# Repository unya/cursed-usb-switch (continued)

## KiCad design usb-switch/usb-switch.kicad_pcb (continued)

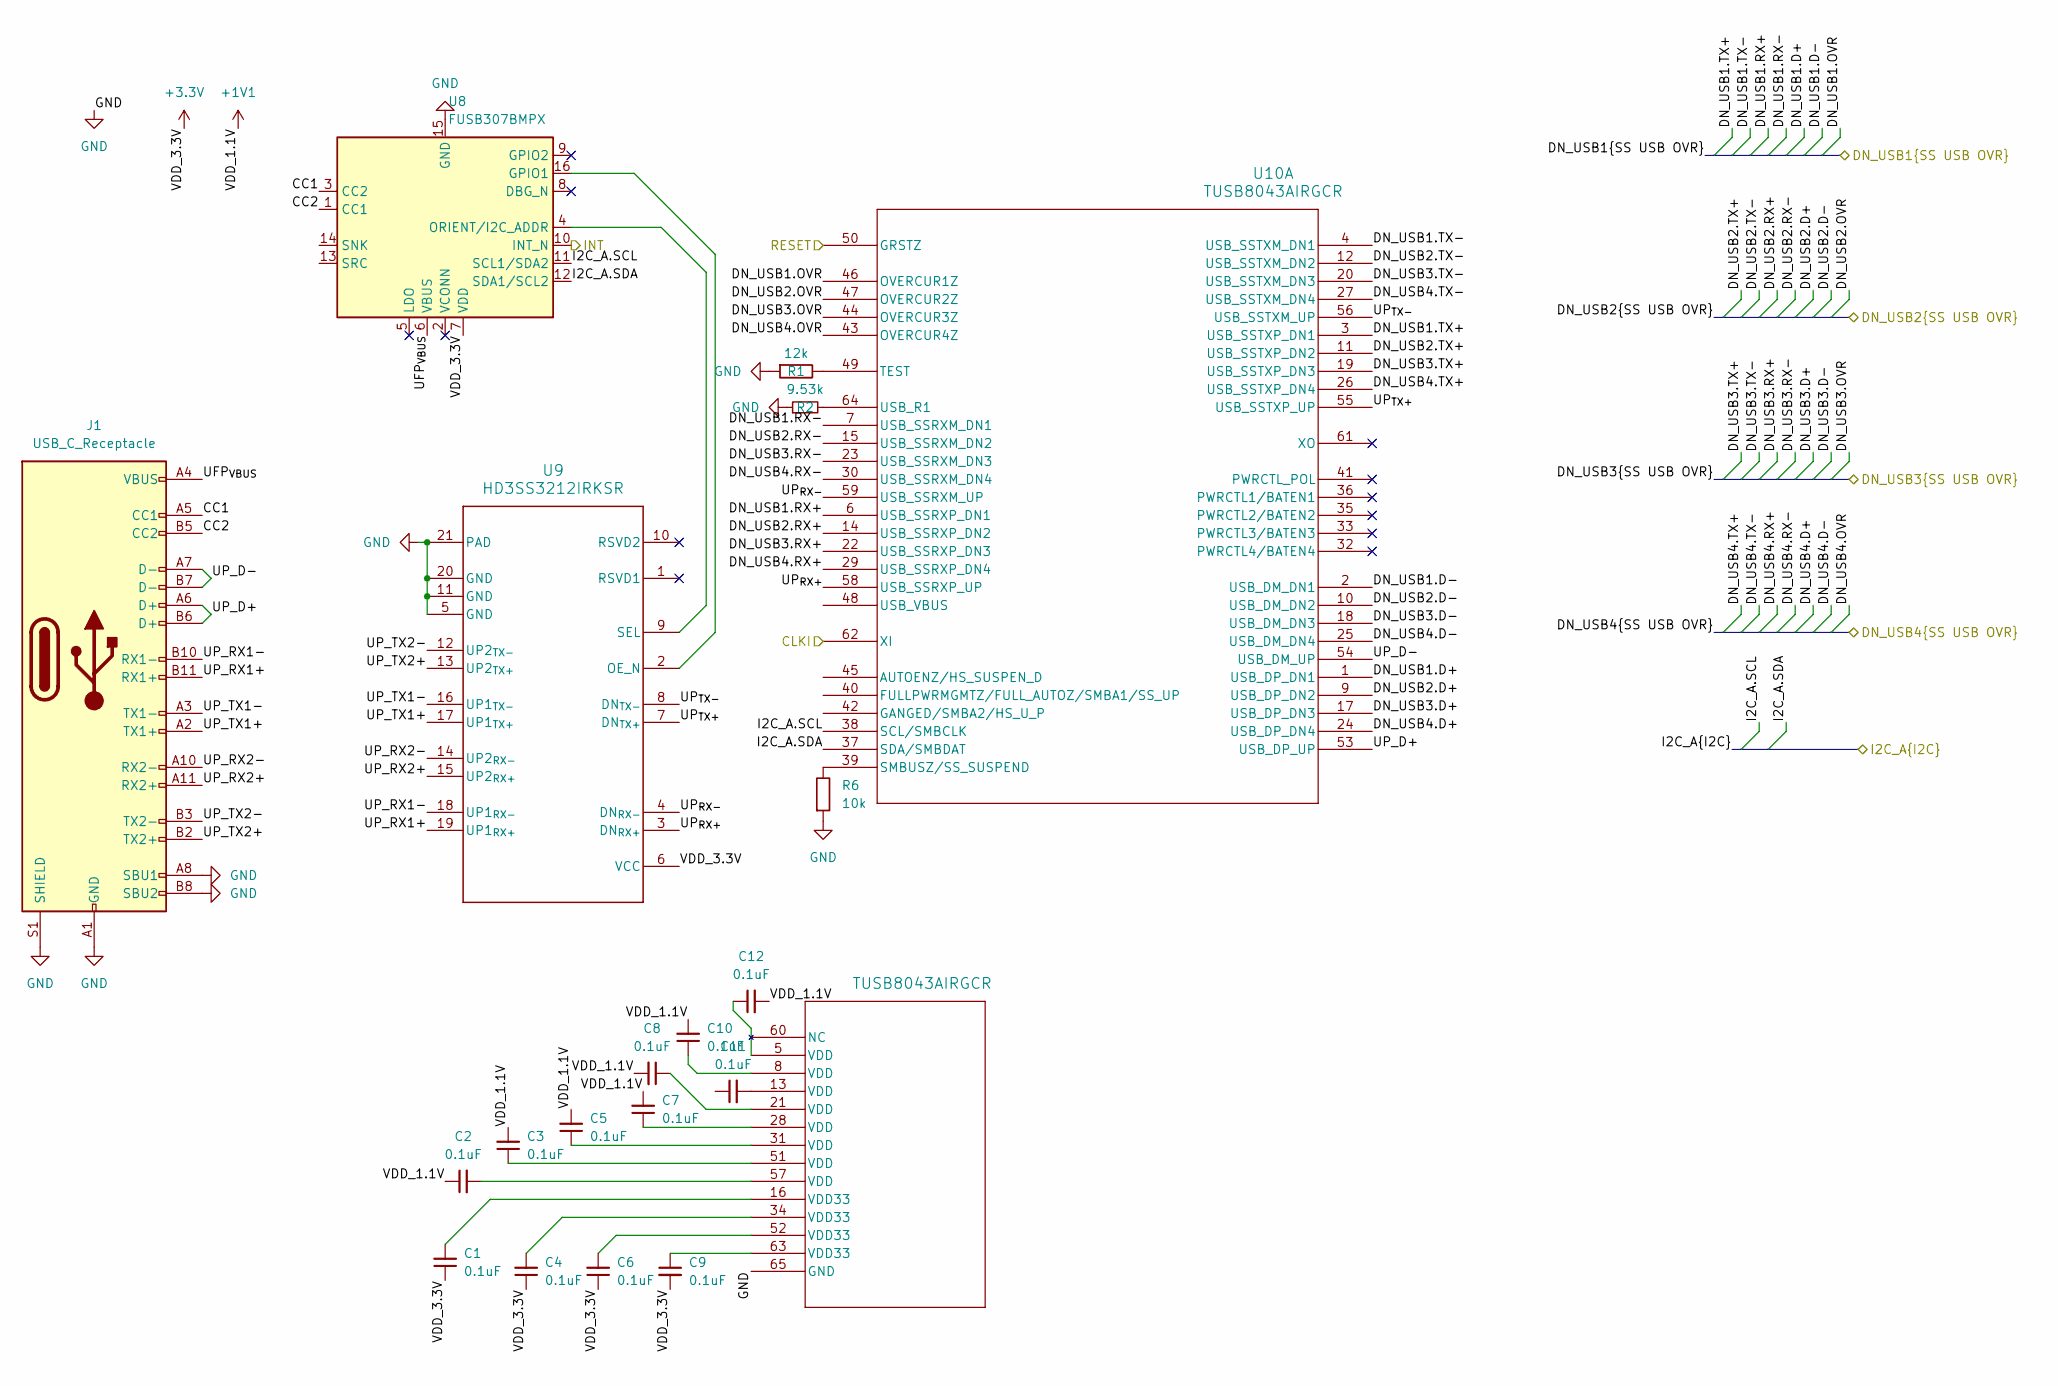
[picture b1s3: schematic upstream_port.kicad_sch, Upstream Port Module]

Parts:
C1, C2, C3, C4, C5, C6, C7, C8, C9, C10, C11, C12: 0.1uF; C_0201_0603Metric
J1: USB_C_Receptacle; USB_C_Receptacle_Amphenol_12401548E4-2A
R1: 12k; R_0201_0603Metric
R2: 9.53k; R_0201_0603Metric
R6: 10k; R_0201_0603Metric
U8: FUSB307BMPX; WQFN-16-1EP_3x3mm_P0.5mm_EP1.75x1.75mm
U9: HD3SS3212IRKSR; RKS0020A
U10: TUSB8043AIRGCR; VQFN64_RGC_TEX

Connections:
+1V1: C2.1, C3.2, C5.2, C7.2, C8.2, C10.2, C12.2; also elsewhere on the board
+3.3V: C1.1, C4.1, C6.1, C9.2, U8.7 (VDD), U9.6 (VCC); also elsewhere on the board
/I2C_A.SCL: U8.11 (SCL1/SDA2), U10.38 (SCL/SMBCLK); also elsewhere on the board
/I2C_A.SDA: U8.12 (SDA1/SCL2), U10.37 (SDA/SMBDAT); also elsewhere on the board
/LNK_1-1.D+: U10.1 (USB_DP_DN1); also elsewhere on the board
/LNK_1-1.D-: U10.2 (USB_DM_DN1); also elsewhere on the board
/LNK_1-1.OVR: U10.46 (OVERCUR1Z)
/LNK_1-1.RX+: U10.6 (USB_SSRXP_DN1); also elsewhere on the board
/LNK_1-1.RX-: U10.7 (USB_SSRXM_DN1); also elsewhere on the board
/LNK_1-1.TX+: U10.3 (USB_SSTXP_DN1); also elsewhere on the board
/LNK_1-1.TX-: U10.4 (USB_SSTXM_DN1); also elsewhere on the board
/LNK_1-2.D+: U10.9 (USB_DP_DN2); also elsewhere on the board
/LNK_1-2.D-: U10.10 (USB_DM_DN2); also elsewhere on the board
/LNK_1-2.OVR: U10.47 (OVERCUR2Z)
/LNK_1-2.RX+: U10.14 (USB_SSRXP_DN2); also elsewhere on the board
/LNK_1-2.RX-: U10.15 (USB_SSRXM_DN2); also elsewhere on the board
/LNK_1-2.TX+: U10.11 (USB_SSTXP_DN2); also elsewhere on the board
/LNK_1-2.TX-: U10.12 (USB_SSTXM_DN2); also elsewhere on the board
/LNK_1-3.D+: U10.17 (USB_DP_DN3); also elsewhere on the board
/LNK_1-3.D-: U10.18 (USB_DM_DN3); also elsewhere on the board
/LNK_1-3.OVR: U10.44 (OVERCUR3Z)
/LNK_1-3.RX+: U10.22 (USB_SSRXP_DN3); also elsewhere on the board
/LNK_1-3.RX-: U10.23 (USB_SSRXM_DN3); also elsewhere on the board
/LNK_1-3.TX+: U10.19 (USB_SSTXP_DN3); also elsewhere on the board
/LNK_1-3.TX-: U10.20 (USB_SSTXM_DN3); also elsewhere on the board
/LNK_1-4.D+: U10.24 (USB_DP_DN4); also elsewhere on the board
/LNK_1-4.D-: U10.25 (USB_DM_DN4); also elsewhere on the board
/LNK_1-4.OVR: U10.43 (OVERCUR4Z)
/LNK_1-4.RX+: U10.29 (USB_SSRXP_DN4); also elsewhere on the board
/LNK_1-4.RX-: U10.30 (USB_SSRXM_DN4); also elsewhere on the board
/LNK_1-4.TX+: U10.26 (USB_SSTXP_DN4); also elsewhere on the board
/LNK_1-4.TX-: U10.27 (USB_SSTXM_DN4); also elsewhere on the board
/UFP_INT1: U8.10 (INT_N); also elsewhere on the board
/USBCLK: U10.62 (XI); also elsewhere on the board
/Upstream-port1/CC1: J1.A5 (CC1), U8.3 (CC2)
/Upstream-port1/CC2: J1.B5 (CC2), U8.1 (CC1)
/Upstream-port1/RESET: U10.50 (GRSTZ)
/Upstream-port1/UFP_{VBUS}: J1.A4 (VBUS), J1.A9 (VBUS), J1.B4 (VBUS), J1.B9 (VBUS), U8.6 (VBUS)
/Upstream-port1/UP_D+: J1.A6 (D+), J1.B6 (D+), U10.53 (USB_DP_UP)
/Upstream-port1/UP_D-: J1.A7 (D-), J1.B7 (D-), U10.54 (USB_DM_UP)
/Upstream-port1/UP_RX1+: J1.B11 (RX1+), U9.19 (UP1_{RX+})
/Upstream-port1/UP_RX1-: J1.B10 (RX1-), U9.18 (UP1_{RX-})
/Upstream-port1/UP_RX2+: J1.A11 (RX2+), U9.15 (UP2_{RX+})
/Upstream-port1/UP_RX2-: J1.A10 (RX2-), U9.14 (UP2_{RX-})
/Upstream-port1/UP_TX1+: J1.A2 (TX1+), U9.17 (UP1_{TX+})
/Upstream-port1/UP_TX1-: J1.A3 (TX1-), U9.16 (UP1_{TX-})
/Upstream-port1/UP_TX2+: J1.B2 (TX2+), U9.13 (UP2_{TX+})
/Upstream-port1/UP_TX2-: J1.B3 (TX2-), U9.12 (UP2_{TX-})
/Upstream-port1/UP_{RX+}: U9.3 (DN_{RX+}), U10.58 (USB_SSRXP_UP)
/Upstream-port1/UP_{RX-}: U9.4 (DN_{RX-}), U10.59 (USB_SSRXM_UP)
/Upstream-port1/UP_{TX+}: U9.7 (DN_{TX+}), U10.55 (USB_SSTXP_UP)
/Upstream-port1/UP_{TX-}: U9.8 (DN_{TX-}), U10.56 (USB_SSTXM_UP)
GND: J1.A1 (GND), J1.A8 (SBU1), J1.A12 (GND), J1.B1 (GND), J1.B8 (SBU2), J1.B12 (GND), J1.S1 (SHIELD), R1.1, R2.1, R6.1, U8.15 (GND), U8.17 (GND), U9.5 (GND), U9.11 (GND), U9.20 (GND), U9.21 (PAD), U10.65 (GND); also elsewhere on the board
unnamed: C1.2, U10.16 (VDD33)
unnamed: C2.2, U10.57 (VDD)
unnamed: C3.1, U10.51 (VDD)
unnamed: C4.2, U10.34 (VDD33)
unnamed: C5.1, U10.31 (VDD)
unnamed: C6.2, U10.52 (VDD33)
unnamed: C7.1, U10.28 (VDD)
unnamed: C8.1, U10.21 (VDD)
unnamed: C9.1, U10.63 (VDD33)
unnamed: C10.1, U10.8 (VDD)
unnamed: C11.2, U10.13 (VDD)
unnamed: C12.1, U10.5 (VDD)
unnamed: U8.16 (GPIO1), U9.2 (OE_N)
unnamed: U8.4 (ORIENT/I2C_ADDR), U9.9 (SEL)
unnamed: R1.2, U10.49 (TEST)
unnamed: R2.2, U10.64 (USB_R1)

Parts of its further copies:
C13, C14, C15, C16, C17, C18, C19, C20, C21, C22, C23, C24, C25, C26, C27, C28, C29, C30, C31, C32, C33, C34, C35, C36, C37, C38, C39, C40, C41, C42, C43, C44, C45, C46, C47, C48: 0.1uF; C_0201_0603Metric
J2, J3, J4: USB_C_Receptacle; USB_C_Receptacle_Amphenol_12401548E4-2A
R3, R9, R12: 10k; R_0201_0603Metric
R4, R7, R10: 12k; R_0201_0603Metric
R5, R8, R11: 9.53k; R_0201_0603Metric
U11, U14, U17: FUSB307BMPX; WQFN-16-1EP_3x3mm_P0.5mm_EP1.75x1.75mm
U12, U15, U18: HD3SS3212IRKSR; RKS0020A
U13, U16, U19: TUSB8043AIRGCR; VQFN64_RGC_TEX

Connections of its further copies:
+1V1: C14.1, C15.2, C17.2, C19.2, C20.2, C22.2, C24.2, C26.1, C27.2, C29.2, C31.2, C32.2, C34.2, C36.2, C38.1, C39.2, C41.2, C43.2, C44.2, C46.2, C48.2; also elsewhere on the board
+3.3V: C13.1, C16.1, C18.1, C21.2, C25.1, C28.1, C30.1, C33.2, C37.1, C40.1, C42.1, C45.2, U11.7 (VDD), U12.6 (VCC), U14.7 (VDD), U15.6 (VCC), U17.7 (VDD), U18.6 (VCC); also elsewhere on the board
/I2C_B.SCL: U11.11 (SCL1/SDA2), U13.38 (SCL/SMBCLK); also elsewhere on the board
/I2C_B.SDA: U11.12 (SDA1/SCL2), U13.37 (SDA/SMBDAT); also elsewhere on the board
/I2C_C.SCL: U14.11 (SCL1/SDA2), U16.38 (SCL/SMBCLK); also elsewhere on the board
/I2C_C.SDA: U14.12 (SDA1/SCL2), U16.37 (SDA/SMBDAT); also elsewhere on the board
/I2C_D.SCL: U17.11 (SCL1/SDA2), U19.38 (SCL/SMBCLK); also elsewhere on the board
/I2C_D.SDA: U17.12 (SDA1/SCL2), U19.37 (SDA/SMBDAT); also elsewhere on the board
/LNK_2-1.D+: U13.1 (USB_DP_DN1); also elsewhere on the board
/LNK_2-1.D-: U13.2 (USB_DM_DN1); also elsewhere on the board
/LNK_2-1.OVR: U13.46 (OVERCUR1Z)
/LNK_2-1.RX+: U13.6 (USB_SSRXP_DN1); also elsewhere on the board
/LNK_2-1.RX-: U13.7 (USB_SSRXM_DN1); also elsewhere on the board
/LNK_2-1.TX+: U13.3 (USB_SSTXP_DN1); also elsewhere on the board
/LNK_2-1.TX-: U13.4 (USB_SSTXM_DN1); also elsewhere on the board
/LNK_2-2.D+: U13.9 (USB_DP_DN2); also elsewhere on the board
/LNK_2-2.D-: U13.10 (USB_DM_DN2); also elsewhere on the board
/LNK_2-2.OVR: U13.47 (OVERCUR2Z)
/LNK_2-2.RX+: U13.14 (USB_SSRXP_DN2); also elsewhere on the board
/LNK_2-2.RX-: U13.15 (USB_SSRXM_DN2); also elsewhere on the board
/LNK_2-2.TX+: U13.11 (USB_SSTXP_DN2); also elsewhere on the board
/LNK_2-2.TX-: U13.12 (USB_SSTXM_DN2); also elsewhere on the board
/LNK_2-3.D+: U13.17 (USB_DP_DN3); also elsewhere on the board
/LNK_2-3.D-: U13.18 (USB_DM_DN3); also elsewhere on the board
/LNK_2-3.OVR: U13.44 (OVERCUR3Z)
/LNK_2-3.RX+: U13.22 (USB_SSRXP_DN3); also elsewhere on the board
/LNK_2-3.RX-: U13.23 (USB_SSRXM_DN3); also elsewhere on the board
/LNK_2-3.TX+: U13.19 (USB_SSTXP_DN3); also elsewhere on the board
/LNK_2-3.TX-: U13.20 (USB_SSTXM_DN3); also elsewhere on the board
/LNK_2-4.D+: U13.24 (USB_DP_DN4); also elsewhere on the board
/LNK_2-4.D-: U13.25 (USB_DM_DN4); also elsewhere on the board
/LNK_2-4.OVR: U13.43 (OVERCUR4Z)
/LNK_2-4.RX+: U13.29 (USB_SSRXP_DN4); also elsewhere on the board
/LNK_2-4.RX-: U13.30 (USB_SSRXM_DN4); also elsewhere on the board
/LNK_2-4.TX+: U13.26 (USB_SSTXP_DN4); also elsewhere on the board
/LNK_2-4.TX-: U13.27 (USB_SSTXM_DN4); also elsewhere on the board
/LNK_3-1.D+: U16.1 (USB_DP_DN1); also elsewhere on the board
/LNK_3-1.D-: U16.2 (USB_DM_DN1); also elsewhere on the board
/LNK_3-1.OVR: U16.46 (OVERCUR1Z)
/LNK_3-1.RX+: U16.6 (USB_SSRXP_DN1); also elsewhere on the board
/LNK_3-1.RX-: U16.7 (USB_SSRXM_DN1); also elsewhere on the board
/LNK_3-1.TX+: U16.3 (USB_SSTXP_DN1); also elsewhere on the board
/LNK_3-1.TX-: U16.4 (USB_SSTXM_DN1); also elsewhere on the board
/LNK_3-2.D+: U16.9 (USB_DP_DN2); also elsewhere on the board
/LNK_3-2.D-: U16.10 (USB_DM_DN2); also elsewhere on the board
/LNK_3-2.OVR: U16.47 (OVERCUR2Z)
/LNK_3-2.RX+: U16.14 (USB_SSRXP_DN2); also elsewhere on the board
/LNK_3-2.RX-: U16.15 (USB_SSRXM_DN2); also elsewhere on the board
/LNK_3-2.TX+: U16.11 (USB_SSTXP_DN2); also elsewhere on the board
/LNK_3-2.TX-: U16.12 (USB_SSTXM_DN2); also elsewhere on the board
/LNK_3-3.D+: U16.17 (USB_DP_DN3); also elsewhere on the board
/LNK_3-3.D-: U16.18 (USB_DM_DN3); also elsewhere on the board
/LNK_3-3.OVR: U16.44 (OVERCUR3Z)
/LNK_3-3.RX+: U16.22 (USB_SSRXP_DN3); also elsewhere on the board
/LNK_3-3.RX-: U16.23 (USB_SSRXM_DN3); also elsewhere on the board
/LNK_3-3.TX+: U16.19 (USB_SSTXP_DN3); also elsewhere on the board
/LNK_3-3.TX-: U16.20 (USB_SSTXM_DN3); also elsewhere on the board
/LNK_3-4.D+: U16.24 (USB_DP_DN4); also elsewhere on the board
/LNK_3-4.D-: U16.25 (USB_DM_DN4); also elsewhere on the board
/LNK_3-4.OVR: U16.43 (OVERCUR4Z)
/LNK_3-4.RX+: U16.29 (USB_SSRXP_DN4); also elsewhere on the board
/LNK_3-4.RX-: U16.30 (USB_SSRXM_DN4); also elsewhere on the board
/LNK_3-4.TX+: U16.26 (USB_SSTXP_DN4); also elsewhere on the board
/LNK_3-4.TX-: U16.27 (USB_SSTXM_DN4); also elsewhere on the board
/LNK_4-1.D+: U19.1 (USB_DP_DN1); also elsewhere on the board
/LNK_4-1.D-: U19.2 (USB_DM_DN1); also elsewhere on the board
/LNK_4-1.OVR: U19.46 (OVERCUR1Z)
/LNK_4-1.RX+: U19.6 (USB_SSRXP_DN1); also elsewhere on the board
/LNK_4-1.RX-: U19.7 (USB_SSRXM_DN1); also elsewhere on the board
/LNK_4-1.TX+: U19.3 (USB_SSTXP_DN1); also elsewhere on the board
/LNK_4-1.TX-: U19.4 (USB_SSTXM_DN1)
/LNK_4-2.D+: U19.9 (USB_DP_DN2); also elsewhere on the board
/LNK_4-2.D-: U19.10 (USB_DM_DN2); also elsewhere on the board
/LNK_4-2.OVR: U19.47 (OVERCUR2Z)
/LNK_4-2.RX+: U19.14 (USB_SSRXP_DN2); also elsewhere on the board
/LNK_4-2.RX-: U19.15 (USB_SSRXM_DN2); also elsewhere on the board
/LNK_4-2.TX+: U19.11 (USB_SSTXP_DN2); also elsewhere on the board
/LNK_4-2.TX-: U19.12 (USB_SSTXM_DN2)
/LNK_4-3.D+: U19.17 (USB_DP_DN3); also elsewhere on the board
/LNK_4-3.D-: U19.18 (USB_DM_DN3); also elsewhere on the board
/LNK_4-3.OVR: U19.44 (OVERCUR3Z)
/LNK_4-3.RX+: U19.22 (USB_SSRXP_DN3); also elsewhere on the board
/LNK_4-3.RX-: U19.23 (USB_SSRXM_DN3); also elsewhere on the board
/LNK_4-3.TX+: U19.19 (USB_SSTXP_DN3); also elsewhere on the board
/LNK_4-3.TX-: U19.20 (USB_SSTXM_DN3)
/LNK_4-4.D+: U19.24 (USB_DP_DN4); also elsewhere on the board
/LNK_4-4.D-: U19.25 (USB_DM_DN4); also elsewhere on the board
/LNK_4-4.OVR: U19.43 (OVERCUR4Z)
/LNK_4-4.RX+: U19.29 (USB_SSRXP_DN4); also elsewhere on the board
/LNK_4-4.RX-: U19.30 (USB_SSRXM_DN4); also elsewhere on the board
/LNK_4-4.TX+: U19.26 (USB_SSTXP_DN4); also elsewhere on the board
/LNK_4-4.TX-: U19.27 (USB_SSTXM_DN4)
/UFP_INT2: U11.10 (INT_N); also elsewhere on the board
/UFP_INT3: U14.10 (INT_N); also elsewhere on the board
/UFP_INT4: U17.10 (INT_N); also elsewhere on the board
/USBCLK: U13.62 (XI), U16.62 (XI), U19.62 (XI); also elsewhere on the board
/Upstream-port2/CC1: J2.A5 (CC1), U11.3 (CC2)
/Upstream-port2/CC2: J2.B5 (CC2), U11.1 (CC1)
/Upstream-port2/RESET: U13.50 (GRSTZ)
/Upstream-port2/UFP_{VBUS}: J2.A4 (VBUS), J2.A9 (VBUS), J2.B4 (VBUS), J2.B9 (VBUS), U11.6 (VBUS)
/Upstream-port2/UP_D+: J2.A6 (D+), J2.B6 (D+), U13.53 (USB_DP_UP)
/Upstream-port2/UP_D-: J2.A7 (D-), J2.B7 (D-), U13.54 (USB_DM_UP)
/Upstream-port2/UP_RX1+: J2.B11 (RX1+), U12.19 (UP1_{RX+})
/Upstream-port2/UP_RX1-: J2.B10 (RX1-), U12.18 (UP1_{RX-})
/Upstream-port2/UP_RX2+: J2.A11 (RX2+), U12.15 (UP2_{RX+})
/Upstream-port2/UP_RX2-: J2.A10 (RX2-), U12.14 (UP2_{RX-})
/Upstream-port2/UP_TX1+: J2.A2 (TX1+), U12.17 (UP1_{TX+})
/Upstream-port2/UP_TX1-: J2.A3 (TX1-), U12.16 (UP1_{TX-})
/Upstream-port2/UP_TX2+: J2.B2 (TX2+), U12.13 (UP2_{TX+})
/Upstream-port2/UP_TX2-: J2.B3 (TX2-), U12.12 (UP2_{TX-})
/Upstream-port2/UP_{RX+}: U12.3 (DN_{RX+}), U13.58 (USB_SSRXP_UP)
/Upstream-port2/UP_{RX-}: U12.4 (DN_{RX-}), U13.59 (USB_SSRXM_UP)
/Upstream-port2/UP_{TX+}: U12.7 (DN_{TX+}), U13.55 (USB_SSTXP_UP)
/Upstream-port2/UP_{TX-}: U12.8 (DN_{TX-}), U13.56 (USB_SSTXM_UP)
/Upstream-port3/CC1: J3.A5 (CC1), U14.3 (CC2)
/Upstream-port3/CC2: J3.B5 (CC2), U14.1 (CC1)
/Upstream-port3/RESET: U16.50 (GRSTZ)
/Upstream-port3/UFP_{VBUS}: J3.A4 (VBUS), J3.A9 (VBUS), J3.B4 (VBUS), J3.B9 (VBUS), U14.6 (VBUS)
/Upstream-port3/UP_D+: J3.A6 (D+), J3.B6 (D+), U16.53 (USB_DP_UP)
/Upstream-port3/UP_D-: J3.A7 (D-), J3.B7 (D-), U16.54 (USB_DM_UP)
/Upstream-port3/UP_RX1+: J3.B11 (RX1+), U15.19 (UP1_{RX+})
/Upstream-port3/UP_RX1-: J3.B10 (RX1-), U15.18 (UP1_{RX-})
/Upstream-port3/UP_RX2+: J3.A11 (RX2+), U15.15 (UP2_{RX+})
/Upstream-port3/UP_RX2-: J3.A10 (RX2-), U15.14 (UP2_{RX-})
/Upstream-port3/UP_TX1+: J3.A2 (TX1+), U15.17 (UP1_{TX+})
/Upstream-port3/UP_TX1-: J3.A3 (TX1-), U15.16 (UP1_{TX-})
/Upstream-port3/UP_TX2+: J3.B2 (TX2+), U15.13 (UP2_{TX+})
/Upstream-port3/UP_TX2-: J3.B3 (TX2-), U15.12 (UP2_{TX-})
/Upstream-port3/UP_{RX+}: U15.3 (DN_{RX+}), U16.58 (USB_SSRXP_UP)
/Upstream-port3/UP_{RX-}: U15.4 (DN_{RX-}), U16.59 (USB_SSRXM_UP)
/Upstream-port3/UP_{TX+}: U15.7 (DN_{TX+}), U16.55 (USB_SSTXP_UP)
/Upstream-port3/UP_{TX-}: U15.8 (DN_{TX-}), U16.56 (USB_SSTXM_UP)
/Upstream-port4/CC1: J4.A5 (CC1), U17.3 (CC2)
/Upstream-port4/CC2: J4.B5 (CC2), U17.1 (CC1)
/Upstream-port4/RESET: U19.50 (GRSTZ)
/Upstream-port4/UFP_{VBUS}: J4.A4 (VBUS), J4.A9 (VBUS), J4.B4 (VBUS), J4.B9 (VBUS), U17.6 (VBUS)
/Upstream-port4/UP_D+: J4.A6 (D+), J4.B6 (D+), U19.53 (USB_DP_UP)
/Upstream-port4/UP_D-: J4.A7 (D-), J4.B7 (D-), U19.54 (USB_DM_UP)
/Upstream-port4/UP_RX1+: J4.B11 (RX1+), U18.19 (UP1_{RX+})
/Upstream-port4/UP_RX1-: J4.B10 (RX1-), U18.18 (UP1_{RX-})
/Upstream-port4/UP_RX2+: J4.A11 (RX2+), U18.15 (UP2_{RX+})
/Upstream-port4/UP_RX2-: J4.A10 (RX2-), U18.14 (UP2_{RX-})
/Upstream-port4/UP_TX1+: J4.A2 (TX1+), U18.17 (UP1_{TX+})
/Upstream-port4/UP_TX1-: J4.A3 (TX1-), U18.16 (UP1_{TX-})
/Upstream-port4/UP_TX2+: J4.B2 (TX2+), U18.13 (UP2_{TX+})
/Upstream-port4/UP_TX2-: J4.B3 (TX2-), U18.12 (UP2_{TX-})
/Upstream-port4/UP_{RX+}: U18.3 (DN_{RX+}), U19.58 (USB_SSRXP_UP)
/Upstream-port4/UP_{RX-}: U18.4 (DN_{RX-}), U19.59 (USB_SSRXM_UP)
/Upstream-port4/UP_{TX+}: U18.7 (DN_{TX+}), U19.55 (USB_SSTXP_UP)
/Upstream-port4/UP_{TX-}: U18.8 (DN_{TX-}), U19.56 (USB_SSTXM_UP)
GND: J2.A1 (GND), J2.A8 (SBU1), J2.A12 (GND), J2.B1 (GND), J2.B8 (SBU2), J2.B12 (GND), J2.S1 (SHIELD), J3.A1 (GND), J3.A8 (SBU1), J3.A12 (GND), J3.B1 (GND), J3.B8 (SBU2), J3.B12 (GND), J3.S1 (SHIELD), J4.A1 (GND), J4.A8 (SBU1), J4.A12 (GND), J4.B1 (GND), J4.B8 (SBU2), J4.B12 (GND), J4.S1 (SHIELD), R3.1, R4.1, R5.1, R7.1, R8.1, R9.1, R10.1, R11.1, R12.1, U11.15 (GND), U11.17 (GND), U12.5 (GND), U12.11 (GND), U12.20 (GND), U12.21 (PAD), U13.65 (GND), U14.15 (GND), U14.17 (GND), U15.5 (GND), U15.11 (GND), U15.20 (GND), U15.21 (PAD), U16.65 (GND), U17.15 (GND), U17.17 (GND), U18.5 (GND), U18.11 (GND), U18.20 (GND), U18.21 (PAD), U19.65 (GND); also elsewhere on the board
unnamed: C13.2, U13.16 (VDD33)
unnamed: C14.2, U13.57 (VDD)
unnamed: C15.1, U13.51 (VDD)
unnamed: C16.2, U13.34 (VDD33)
unnamed: C17.1, U13.31 (VDD)
unnamed: C18.2, U13.52 (VDD33)
unnamed: C19.1, U13.28 (VDD)
unnamed: C20.1, U13.21 (VDD)
unnamed: C21.1, U13.63 (VDD33)
unnamed: C22.1, U13.8 (VDD)
unnamed: C23.2, U13.13 (VDD)
unnamed: C24.1, U13.5 (VDD)
unnamed: C25.2, U16.16 (VDD33)
unnamed: C26.2, U16.57 (VDD)
unnamed: C27.1, U16.51 (VDD)
unnamed: C28.2, U16.34 (VDD33)
unnamed: C29.1, U16.31 (VDD)
unnamed: C30.2, U16.52 (VDD33)
unnamed: C31.1, U16.28 (VDD)
unnamed: C32.1, U16.21 (VDD)
unnamed: C33.1, U16.63 (VDD33)
unnamed: C34.1, U16.8 (VDD)
unnamed: C35.2, U16.13 (VDD)
unnamed: C36.1, U16.5 (VDD)
unnamed: C37.2, U19.16 (VDD33)
unnamed: C38.2, U19.57 (VDD)
unnamed: C39.1, U19.51 (VDD)
unnamed: C40.2, U19.34 (VDD33)
unnamed: C41.1, U19.31 (VDD)
unnamed: C42.2, U19.52 (VDD33)
unnamed: C43.1, U19.28 (VDD)
unnamed: C44.1, U19.21 (VDD)
unnamed: C45.1, U19.63 (VDD33)
unnamed: C46.1, U19.8 (VDD)
unnamed: C47.2, U19.13 (VDD)
unnamed: C48.1, U19.5 (VDD)
unnamed: U11.16 (GPIO1), U12.2 (OE_N)
unnamed: U11.4 (ORIENT/I2C_ADDR), U12.9 (SEL)
unnamed: R4.2, U13.49 (TEST)
unnamed: R5.2, U13.64 (USB_R1)
unnamed: U14.16 (GPIO1), U15.2 (OE_N)
unnamed: U14.4 (ORIENT/I2C_ADDR), U15.9 (SEL)
unnamed: R9.2, U16.39 (SMBUSZ/SS_SUSPEND)
unnamed: R7.2, U16.49 (TEST)
unnamed: R8.2, U16.64 (USB_R1)
unnamed: U17.16 (GPIO1), U18.2 (OE_N)
unnamed: U17.4 (ORIENT/I2C_ADDR), U18.9 (SEL)
unnamed: R12.2, U19.39 (SMBUSZ/SS_SUSPEND)
unnamed: R10.2, U19.49 (TEST)
unnamed: R11.2, U19.64 (USB_R1)

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
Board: 2 copper layers, 136 parts (0 on the bottom side), 404 nets, no tracks yet.

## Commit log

2024-03-15 Initial commit of the cursed thing
2024-03-15 Added .gitignore with backup folder
2024-03-15 Starting to look closer to completion
2024-03-15 Added some missing I2C and interrupt connections, further organizing of PCB layout
